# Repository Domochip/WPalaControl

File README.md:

# WPalaControl

**WPalaControl** is a Wi-Fi adapter (based on a D1 Mini) to control and monitor stoves using a **Fumis controller** (Palazzetti, Jotul, Godin, ...).

- 🔥 Power on/off, set point, power level, fans, silent mode, chrono programs, parameters
- 📊 Status, alarms, temperatures, counters, pellet consumption, delta pressure
- 🔌 Native HTTP API compatible with existing Palazzetti/Fumis apps and plugins
- 📡 MQTT with Home Assistant auto-discovery
- ⬆️ Online firmware update from GitHub (also as a Home Assistant Update entity)
- 🔒 Optional password protection of the web interface

## Contents

- [WPalaControl](#wpalacontrol)
  - [Contents](#contents)
  - [Quick start](#quick-start)
  - [Stove compatibility](#stove-compatibility)
  - [Home Automation compatibility](#home-automation-compatibility)
  - [Get your adapter](#get-your-adapter)
  - [Connect it to the stove](#connect-it-to-the-stove)
  - [First boot](#first-boot)
  - [Web interface](#web-interface)
    - [Status](#status)
    - [Config](#config)
      - [System](#system)
      - [WiFi](#wifi)
      - [PalaControl](#palacontrol)
      - [PalaControl - Home Automation](#palacontrol---home-automation)
    - [Firmware](#firmware)
  - [Use it](#use-it)
    - [HTTP](#http)
    - [MQTT](#mqtt)
  - [Command list](#command-list)
  - [Published MQTT values](#published-mqtt-values)
  - [Troubleshooting](#troubleshooting)
  - [Recovery Mode](#recovery-mode)

## Quick start

1. Check that your stove has a [Fumis controller](#stove-compatibility)
2. Plug the module into the stove with the provided cable (or the [right one](#connect-it-to-the-stove) if you built it yourself)
3. Connect to the `WPalaControl` Wi-Fi network (password: `password`)
4. In **Config**, enter your Wi-Fi credentials and save
5. Open <http://wpalacontrol.local>, then configure MQTT / Home Assistant if needed

## Stove compatibility

WPalaControl works with stoves using the **Fumis controller**, used by many manufacturers:

Palazzetti / Jotul / TurboFonte / Godin / Fonte Flamme / Invicta / Casatelli / Alpis / Faizen / HETA / ...

To check if your stove is compatible, look for one of these control panels or motherboards:

## Home Automation compatibility

| | Integration | Preview |
| --- | --- | --- |
|  | [MQTT Integration](https://www.home-assistant.io/integrations/mqtt/) (auto-discovery)<br>Most options and fan controls |  |
|  | [Palazzetti Integration](https://www.home-assistant.io/integrations/palazzetti)<br>(Home Assistant 2024.11 minimum)<br>Basic implementation for now |  |
|  | [Palazzetti plugin](https://www.jeedom.com/market/index.php?v=d&p=market_display&id=3104) |  |

## Get your adapter

- 🛍️ **Ready to use**: I produce small batches, available here:
  
- 🔧 **Build it yourself**: schematic, PCB, box and firmware are described in [BUILD](BUILD.md)

## Connect it to the stove

- ✅ If your stove has an accessible RJ12 connector, simply plug the cable in.
- 🔍 If not, you need an additional cable and a splitter: see [Splitter Cabling](SPLITTERCABLING.md).

If you bought your WPalaControl ready to use, the right cable is provided: simply use it.

> [!WARNING]
> If you built it yourself (or use another cable), use the correct cable for your hardware version (written on the PCB):
>
> - Hardware **V1.x**: **crossed** cable
> - Hardware **V2.x**: **straight** cable

## First boot

On first boot, the module creates its own Wi-Fi network (AP mode):

| Firmware | SSID | Password |
| --- | --- | --- |
| 3.2.0 and higher | `WPalaControl` | `password` |
| 3.1.x and lower | `WirelessPalaControlXXXX` | `PasswordPalaControl` |

You should be redirected to the module page automatically. If not, go to <http://192.168.4.1>.

Once the module is connected to your Wi-Fi network, it is reachable at 👉 <http://wpalacontrol.local> 👈

> [!NOTE]
> The access point is only started when the module is not connected to your Wi-Fi network (first boot, wrong settings, network down).

## Web interface

### Status

- **System**: module serial number, firmware version, uptime, local time (NTP) and free memory. Logged crashes are listed if any
- **WiFi**: MAC address, Access Point status (and IP), Station status with connection state, IP, IP source (DHCP or Static IP), BSSID and signal strength (RSSI)
- **WPalaControl**:
  - **Hardware Version**: detected (or forced) hardware version of the module
  - **Stove infos**: the stove SN appears first, then all stove values are refreshed live every "Upload Period" (values that changed are shown in bold)
  - **Home Automation Status**: protocol, MQTT connection state and result of the last publish

### Config

#### System

- **NTP Timezone**: your timezone, used for the module local time (default: Europe/Paris)
- **Web Password**: protects the web interface with a password (user: `admin`). Leave empty to disable authentication (default). The password is never requested from devices connected to the module's own Wi-Fi network (AP mode). The HTTP API used by home automation systems stays reachable without password for compatibility reasons (see [HTTP](#http))
- **Reboot**: restart the module
- **Reset Configuration**: erase all settings (System, WiFi, PalaControl) and restart the module with its default configuration (after a confirmation). The module then starts its own Wi-Fi network (AP mode, see [First boot](#first-boot)) and is reachable at <http://192.168.4.1>

#### WiFi

- **SSID & Password**: credentials of your Wi-Fi network. Nearby networks are listed in the dropdown next to the SSID field (strongest signal first)
- **Hostname**: name of the module on the network
- **Static IP**: check to use a fixed IP configuration instead of DHCP
  - **IP, NetMask, Gateway, DNS 1 & 2**: fixed IP configuration (IP is required)

Leave the SSID empty to keep the module in AP mode (reachable at <http://192.168.4.1>).

#### PalaControl

- **Hardware detection**: hardware version of the module
  - **Auto** (default): version is detected automatically at boot
  - **V1.X** / **V2.X**: force the hardware version if auto-detection fails

#### PalaControl - Home Automation

- **Type**: enable/disable MQTT communication
- **Upload Period**: refresh interval of stove information (15 to 300 seconds)
- **Hostname, Port, Username, Password**: MQTT broker details (username and password are optional)
- **Base Topic**: prefix of all WPalaControl topics
- **MQTT Type**: defines MQTT topics and data structure:
  - **Generic**: raw values under the base topic (e.g. `{baseTopic}/T1` = `20.00`)
  - **Generic JSON**: a JSON per category (e.g. `{baseTopic}/TMPS` = `{"INFO":{"CMD":"GET TMPS","RSP":"OK"},...}`)
  - **Generic Categorized**: raw values under a category topic (e.g. `{baseTopic}/TMPS/T1` = `20.00`)
- **Home Assistant Discovery**: enable/disable Home Assistant auto-discovery
  - **0.2° SetPoint step**: Set Point is adjusted in Home Assistant by 0.2°C steps (using `SET+STPF`) instead of 1°C steps (using `SET+SETP`). Only shown if Home Assistant Discovery is enabled and the stove supports it (air stoves)

### Firmware

- **Current Firmware**: version installed on the module
- **Online Update**: latest release published on [GitHub](https://github.com/Domochip/WPalaControl/releases) (version, title, date, summary and link)
  - **Refresh**: check GitHub again for the latest release
  - **Update**: download and install the latest release (enabled only if a newer version is available)
- **Manual Update**: upload a firmware file downloaded from the [releases page](https://github.com/Domochip/WPalaControl/releases)
  - Expected file name: `WPalaControl.x.y.z.bin`
  - Older `WirelessPalaControl.*.bin` files are also accepted

> [!CAUTION]
> Do not power off the module during the update. It reboots automatically when the update is done.

- ℹ️ Online Update requires Internet access from the module (not available in AP mode). If you configured a static IP, make sure Gateway and DNS are set (not needed with DHCP).
- 🏠 With MQTT and Home Assistant Discovery enabled, a firmware **Update** entity is also available in Home Assistant (checked once a day).

## Use it

Commands are the same for HTTP and MQTT: see the [Command list](#command-list).

### HTTP

Send an HTTP GET request to the module:

```text
http://wpalacontrol.local/cgi-bin/sendmsg.lua?cmd={command}
```

This API never requires the **Web Password**, so existing apps and plugins keep working when it is set.

Example: `http://wpalacontrol.local/cgi-bin/sendmsg.lua?cmd=GET+TMPS` returns:

```json
{"INFO":{"CMD":"GET TMPS","RSP":"OK"},"DATA":{"T1":20.6,"T2":21,"T3":18,"T4":0,"T5":0},"SUCCESS":true}
```

### MQTT

Once MQTT is configured, send commands to the `{baseTopic}/cmd` topic:

```bash
mosquitto_pub -h <broker> -t "WPalaControl/cmd" -m "SET+SETP+21"
```

The result is:

- published following the configured MQTT Type
- published on `{baseTopic}/result` in JSON format

Other topics published by the module:

| Topic | Content |
| --- | --- |
| `{baseTopic}/connected` | `0`: not connected / `1`: connected but no communication with the stove / `2`: module and stove connected |
| `{baseTopic}/Core` | Module status in JSON (manufacturer, model, sn, version, uptime, localtime, freeheap), refreshed every "Upload Period" |
| `{baseTopic}/WiFi` | Wi-Fi status in JSON (apmode, stationmode, stationip, bssid, rssi, ...), refreshed every "Upload Period" |
| `{baseTopic}/App` | WPalaControl status in JSON (hwversion, hwdetection, MQTT status, last publish result, ...), refreshed every "Upload Period" |
| `{baseTopic}/update` | Latest available firmware update information |
| `{baseTopic}/update/install` | Command topic to trigger a firmware update (used by Home Assistant) |

## Command list

⏲️: Published automatically every "Upload Period" (MQTT)  
✨: WPalaControl specific command

| Command | Description | Values | Notes |
| ------- | ----------- | ------ | :---: |
| `GET+STDT` | Get static data | | |
| `GET+ALLS` | Get all status data | | |
| `GET+STAT` | Get stove status | | ⏲️ |
| `GET+TMPS` | Get stove temperatures | | ⏲️ |
| `GET+FAND` | Get fan values | | ⏲️ |
| `GET+SETP` | Get current Set Point (desired temperature) | | ⏲️ |
| `GET+POWR` | Get current power | 1-5 | ⏲️ |
| `GET+CUNT` | Get counters | | |
| `GET+CNTR` | Get counters (same as `GET+CUNT`) | | ⏲️ |
| `GET+DPRS` | Get delta pressure data | | ⏲️ |
| `GET+TIME` | Get stove clock data | | ⏲️ |
| `GET+IOPT` | Get IO ports status | | |
| `GET+SERN` | Get stove Serial Number | | |
| `GET+MDVE` | Get stove model and firmware version | | |
| `GET+CHRD` | Get chrono data | | |
| `GET+PARM+92` | Get parameter (e.g. 92 = pellet type) | parameter number | |
| `GET+HPAR+57` | Get hidden parameter (e.g. 57 = % of pellet to feed for pellet type 3) | parameter number | |
| `BKP+PARM+CSV` | Get all parameters in a CSV file (HTTP only) | | ✨ |
| `BKP+PARM+JSON` | Get all parameters in a JSON file (HTTP only) | | ✨ |
| `BKP+HPAR+CSV` | Get all hidden parameters in a CSV file (HTTP only) | | ✨ |
| `BKP+HPAR+JSON` | Get all hidden parameters in a JSON file (HTTP only) | | ✨ |
| `CMD+ON` | Turn stove ON | | |
| `CMD+OFF` | Turn stove OFF | | |
| `SET+POWR+3` | Set power | 1-5 | |
| `SET+PWRU` | Increase power by 1 unit | | |
| `SET+PWRD` | Decrease power by 1 unit | | |
| `SET+SETP+20` | Set Set Point (desired temperature) | temperature | |
| `SET+STPF+19.8` | Set Set Point with 0.2°C precision (depends on your stove model) | temperature | ✨ |
| `SET+STPU` | Increase Set Point by 1 unit | | |
| `SET+STPD` | Decrease Set Point by 1 unit | | |
| `SET+RFAN+7` | Set Room Fan value | 0-5; 6=Max; 7=Auto | |
| `SET+FN2U` | Increase Room Fan by 1 unit | | |
| `SET+FN2D` | Decrease Room Fan by 1 unit | | |
| `SET+FN3L+0` | Set Room Fan 3 value | 0-5 | |
| `SET+FN4L+0` | Set Room Fan 4 value | 0-5 | |
| `SET+SLNT+0` | Set Silent mode | 0-1 | |
| `SET+TIME+2023-12-28+19:42:00` | Set stove date and time | year 2000-2099, month 1-12, day 1-31, hour 0-23, min 0-59, sec 0-59 | |
| `SET+CSST+0` | Set Chrono status | 0-1 | |
| `SET+CSTH+2+18` | Set Chrono Program start hour | prog 1-6, hour 0-23 | |
| `SET+CSTM+2+30` | Set Chrono Program start minute | prog 1-6, min 0-59 | |
| `SET+CSPH+2+22` | Set Chrono Program stop hour | prog 1-6, hour 0-23 | |
| `SET+CSPM+2+45` | Set Chrono Program stop minute | prog 1-6, min 0-59 | |
| `SET+CSET+2+19` | Set Chrono Program Set Point | prog 1-6, temperature | |
| `SET+CDAY+7+3+6` | Set Chrono Program for a week day (Day-Mem-Prog) | day 1-7, mem 1-3, prog 1-6 | |
| `SET+CPRD+1+19+18+30+22+45` | Set Chrono Program data (Prog-Temp-StartH-StartM-StopH-StopM) | prog 1-6, temperature, 0-23, 0-59, 0-23, 0-59 | |
| `SET+PARM+92+2` | Set parameter 92 to value 2 (pellet type) | parameter number, value (e.g. 1-3 for 92) | |
| `SET+HPAR+57+95` | Set hidden parameter 57 to value 95 (% of pellet to feed for pellet type 3) | parameter number, value | |

## Published MQTT values

Values published automatically every "Upload Period":

| Key | Meaning | Unit |
| --- | ------- | ---- |
| `STATUS`, `LSTATUS`, `FSTATUS` | Stove status | |
| `T1`, `T2`, `T3`, `T4`, `T5` | Stove temperatures | °C |
| `F1V`, `F2V`, `F2L`, `F2LF` | Fan values (meaning depends on your stove model) | |
| `F1RPM` | Fan 1 speed | rpm |
| `F3L`, `F4L` | Fan 3 / Fan 4 levels (if supported by the stove) | 0-5 |
| `F3S`, `F4S` | Fan 3 / Fan 4 values (if supported by the stove) | |
| `IGN` | Ignition counter | |
| `IGNERRORS` | Ignition error counter | |
| `POWERTIME` | Total heating time | hour:minute |
| `HEATTIME` | Unknown meaning | hour:minute |
| `SERVICETIME` | Heating time since last maintenance | hour:minute |
| `ONTIME` | Time since last power ON | hour:minute |
| `OVERTMPERRORS` | Overtemperature error counter | |
| `PQT` | Wood pellet consumption | kg |
| `STOVE_DATETIME` | Stove date and time | |
| `STOVE_WDAY` | Stove week day | |
| `SETP` | Current Set Point (desired temperature) | °C |
| `SECO` | ECO Mode restart temperature threshold (PAR50: 6 -> 0.6°C) | °C |
| `BECO` | ECO Mode active | |
| `PWR` | Current power | 1-5 |
| `FDR` | Feeder | |
| `DP_TARGET` | Delta pressure target | mPa |
| `DP_PRESS` | Actual delta pressure | mPa |

## Troubleshooting

| Problem | What to check |
| --- | --- |
| Stove SN never appears on the Status page | Use the provided cable. If you built it yourself, check the cable type: **crossed** for hardware V1.x, **straight** for V2.x. Check also the **Hardware detection** setting |
| `wpalacontrol.local` does not open | Some devices (e.g. Android, some Windows setups) don't support mDNS: use the module IP address (shown in your router) |
| Wrong Wi-Fi settings, module unreachable | If it can't connect, the module starts its own access point: connect to it and go to <http://192.168.4.1>. You can also press the RST button 3 times to start in [Recovery Mode](#recovery-mode) |
| Web Password forgotten | Press the RST button 3 times to start in [Recovery Mode](#recovery-mode): the password is not requested, so you can change it in **Config** → **System** |
| Online Update fails | The module needs Internet access. If you configured a static IP, make sure Gateway and DNS are set (not needed with DHCP) |
| Nothing published on MQTT | **Status** page → **Home Automation Status** shows the connection state and the last publish result |

## Recovery Mode

Recovery Mode gives you access to the module when you can't reach it normally, without losing its configuration. Use it when:

- the module can't be reached after a Wi-Fi settings change (wrong SSID, password or static IP)
- you forgot the **Web Password**

**Enter Recovery Mode**:

- press the **RST** button (accessible on the side of the box) **3 times in a row**, each press within 5 seconds of the previous one
- only presses of the RST button are counted: unplugging/replugging the module does not trigger Recovery Mode

**In Recovery Mode**:

- the module does not connect to your Wi-Fi network: it only starts its own (SSID and password in [First boot](#first-boot)). Connect to it and go to <http://192.168.4.1>
- the **Web Password** is not requested
- the stored configuration is loaded but not modified: nothing is erased

**Leave Recovery Mode**:

- save any configuration section (e.g. **Config** → **WiFi** or **Config** → **System**), after a confirmation: the module goes back to normal operation immediately (connection to your Wi-Fi network, **Web Password** if set). Reconnect your device to your Wi-Fi network and open the module address
- or reboot the module: it starts normally with its stored configuration

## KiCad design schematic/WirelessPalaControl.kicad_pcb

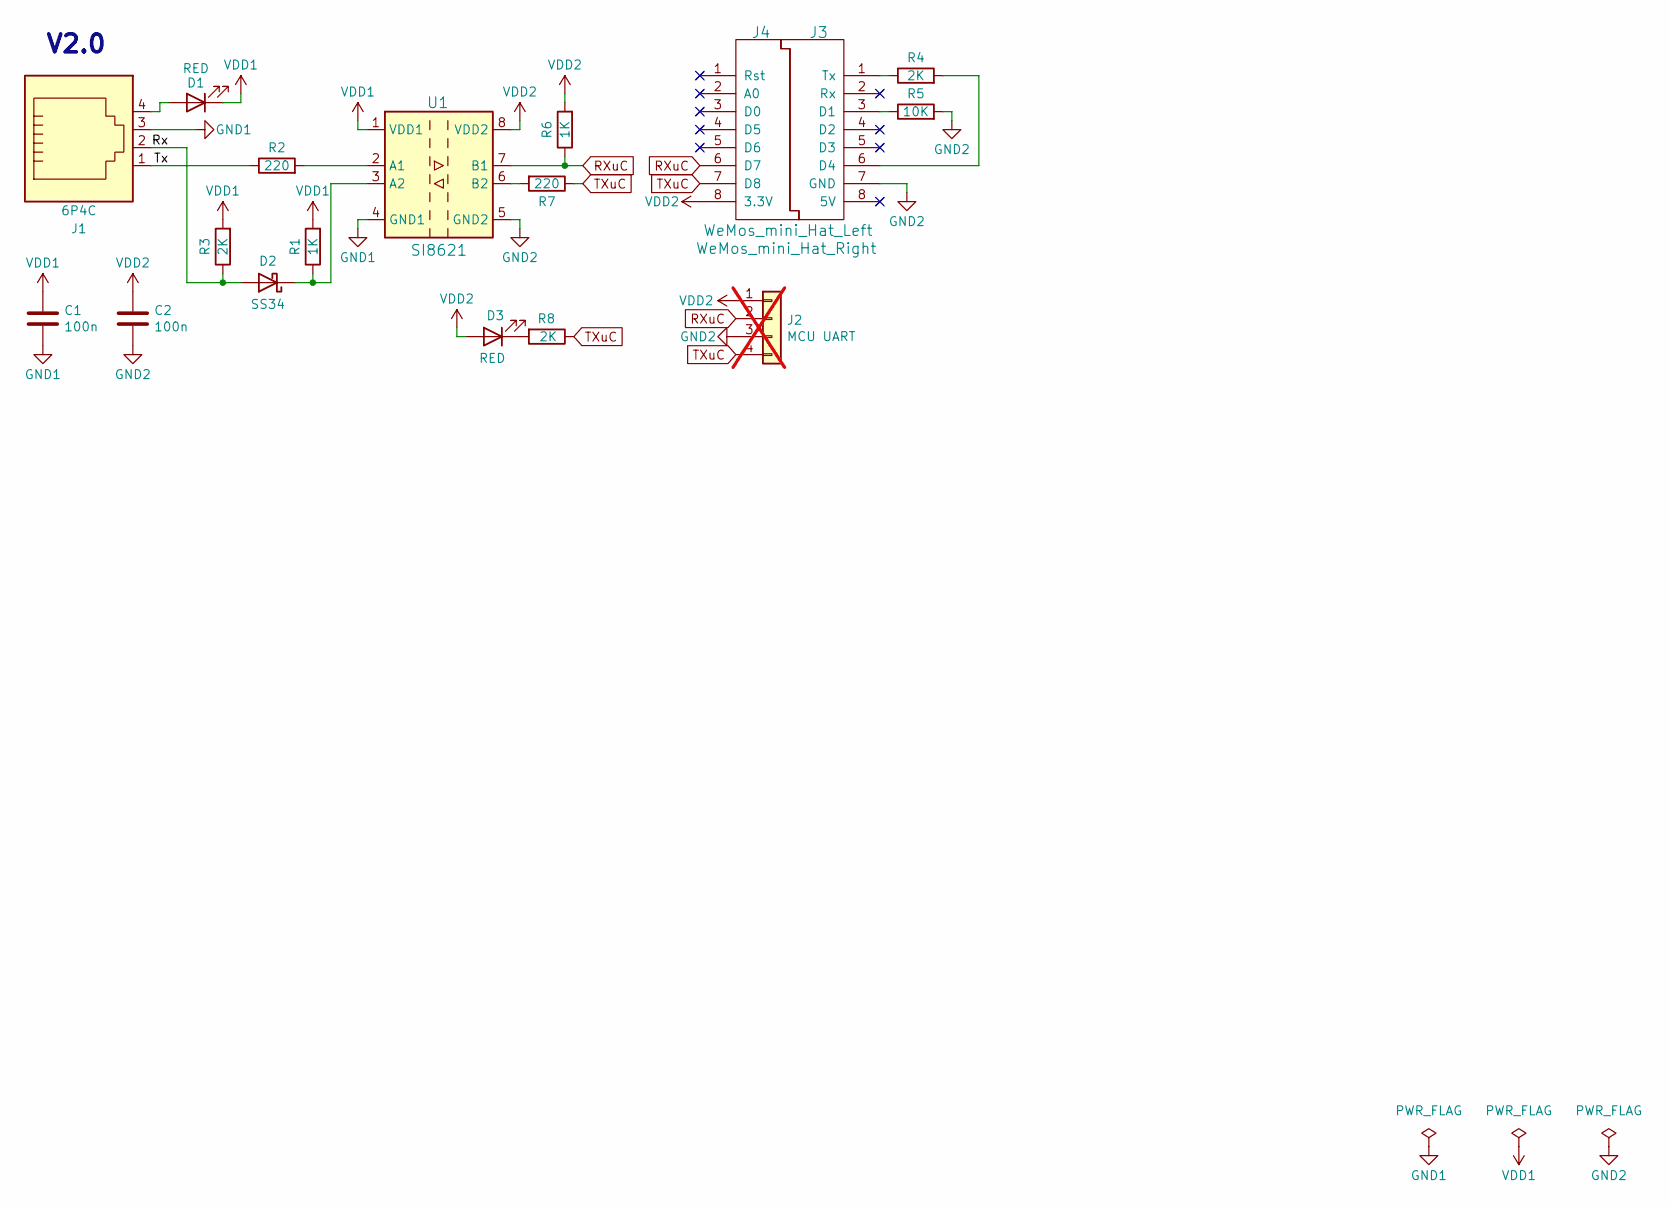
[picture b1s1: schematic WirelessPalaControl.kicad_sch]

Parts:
C1, C2: 100n; C_0805_2012Metric_Pad1.18x1.45mm_HandSolder; LCSC C49678
D1, D3: RED; LED_0805_2012Metric_Pad1.15x1.40mm_HandSolder; LCSC C84256
D2: SS34; D_SMA; LCSC C8678
J1: 6P4C; Ali_RJ11; LCSC C189749
J2: MCU UART; PinHeader_1x04_P2.54mm_Vertical; not fitted
J3: WeMos_mini_Hat_Left; WeMos_D1_mini_Hat_Left; LCSC C7509515
J4: WeMos_mini_Hat_Right; WeMos_D1_mini_Hat_Right; LCSC C7509515
R1, R6: 1K; R_0805_2012Metric_Pad1.20x1.40mm_HandSolder; LCSC C17513
R2, R7: 220; R_0805_2012Metric_Pad1.20x1.40mm_HandSolder; LCSC C17557
R3, R4, R8: 2K; R_0805_2012Metric_Pad1.20x1.40mm_HandSolder; LCSC C17604
R5: 10K; R_0805_2012Metric_Pad1.20x1.40mm_HandSolder; LCSC C17414
U1: SI8621; SOIC-8_3.9x4.9mm_P1.27mm; LCSC C461877

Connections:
/Rx: D2.2 (A), J1.2, R3.1
/Tx: J1.1, R2.1
GND1: C1.2, J1.3, U1.4 (GND1)
GND2: C2.2, J2.3, J3.7 (GND), R5.2, U1.5 (GND2)
unnamed: D1.2 (A), J1.4
unnamed: D2.1 (K), R1.1, U1.3 (A2)
unnamed: D3.1 (K), R8.2
unnamed: J3.3 (D1), R5.1
unnamed: J3.6 (D4), R4.2
unnamed: J3.1 (Tx), R4.1
unnamed: R2.2, U1.2 (A1)
unnamed: R7.2, U1.6 (B2)
RXuC: J2.2, J4.6 (D7), R6.1, U1.7 (B1)
TXuC: J2.4, J4.7 (D8), R7.1, R8.1
VDD1: C1.1, D1.1 (K), R1.2, R3.2, U1.1 (VDD1)
VDD2: C2.1, D3.2 (A), J2.1, J4.8 (3.3V), R6.2, U1.8 (VDD2)

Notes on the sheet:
V2.0

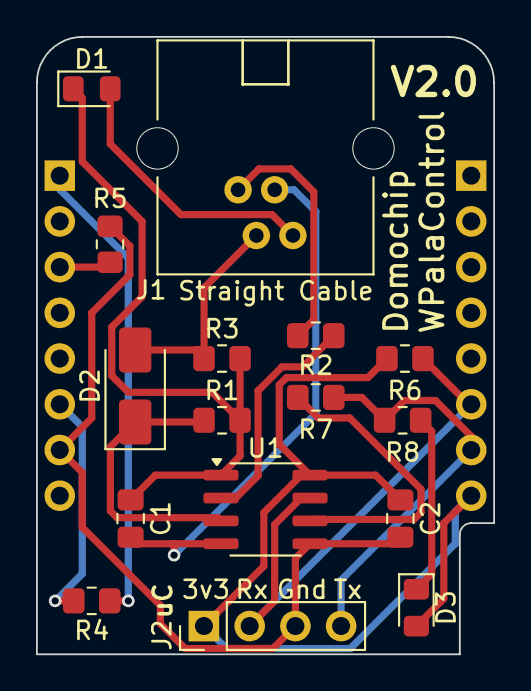
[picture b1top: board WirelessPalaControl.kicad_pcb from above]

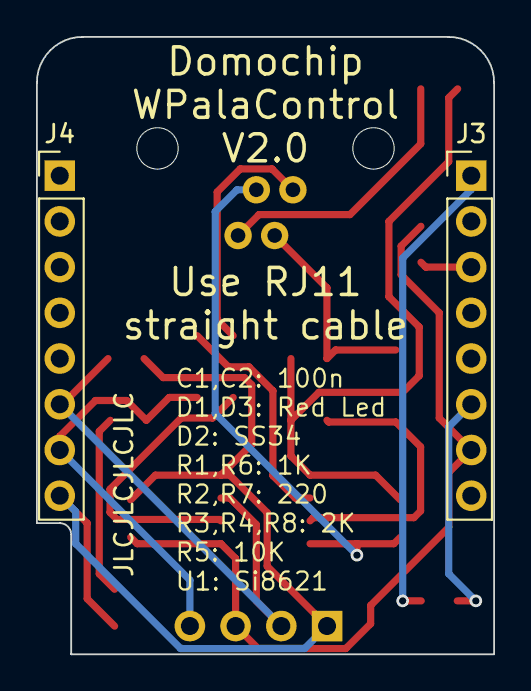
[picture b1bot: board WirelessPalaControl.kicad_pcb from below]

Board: 2 copper layers, 25.4 x 34.3 mm, 18 parts (2 on the bottom side), 16 nets.

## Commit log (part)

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2024-11-12 Rollback duplication of code
2024-11-12 Determine the Main temperature sensor
2024-11-12 Use name for the Main temperature sensor
2024-11-12 Add additionnal sensors for Hydro
2024-11-12 Revert to Room instead of Ambient
2024-11-12 Use Storage Tank wording like docs
2024-11-13 Comment 2nd and 3rd sensor until clarification
2024-11-13 Approach based on Android App
2024-11-13 Better limit condition
2024-11-15 Group FlashString lists
2024-11-15 More usefull variables grouped
2024-11-15 Use new tempProbeTopicListArray variable
2024-11-15 Add Thermostat (climate) entity
2024-11-15 Add Power command to Thermostat
2024-11-15 Add temperature command topic
2024-11-15 Simplify jinja template
2024-11-15 Add Fan management
2024-11-15 Improve jinja templates
2024-11-16 One more usefull flashString
2024-11-23 Change R4 to 2K
2024-11-23 Update schematic and botoom pcb
2024-11-24 Slightly adjust box
2025-09-24 Update schematic and pcb to KiCAD 9
2025-09-25 Adapt WPalaControl for 256dpi/MQTT lib
2025-09-26 Switch to PubSubClient3 lib which is maintained
2025-09-26 Increase MQTT buffer size
2025-09-27 Add coming "default_entity_id" for Home Assistant 2025.10
2025-10-24 Fixed an issue where the WiFi reconnection routine (`_refreshTicker.once()`) never triggered when the initial connection failed. The delay value was incorrectly multiplied by 1000, causing the timer 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
2025-12-22 Fix FAN3 & FAN4 not showing up in Home Assistant
2025-12-23 Fix FAN3 & FAN4 not showing up in Home Assistant (#79)
2025-12-23 Bump version to 3.5.1
2025-12-30 Fix incorrect default_entity_id values
2025-12-30 Bump version to 3.5.2
2026-04-07 Add variables for detection
2026-04-07 Add config field to choose detection mode
2026-04-07 Implement logic for autodetection/forced mode
2026-04-07 Add detection infos on status page
2026-04-07 Force Hardware version instead of autodetection (#87)
    * Add variables for detection
    * Add config field to choose detection mode
    * Implement logic for autodetection/forced mode
    * Add detection infos on status page
2026-04-07 Bump version to 3.5.3
2026-05-13 Update schematic to KiCAD 10
2026-05-13 Reduce String allocation/concatenation in GET CNTR
2026-05-13 Reduce usage of heap
2026-05-13 Factorize baseTopic substring call
2026-05-13 Avoid usage of String.replace to validate strtol conversion
2026-05-13 change type of palaCategory
2026-05-14 Adjust ConfigJSON and StatusJSON functions
2026-05-14 eventSourceBroadcast parameter type is now a char array
2026-05-14 Adapt mqttPublishUpdate according to new parameters an type of fillLatestUpdateInfoJson
2026-05-14 Refactor PalaCmd execution
2026-05-14 Building baseTopic only if required
2026-05-14 Avoid creating a String in heap to check the content
2026-05-15 Adjust for Base 2.7.0
2026-05-15 Revert "Avoid creating a String in heap to check the content"
    This reverts commit 248da516b3f21e527d812d21de225210121652b0.
2026-05-17 Adjust for Base 2.7.1
2026-05-17 Bump version to 3.6.0
2026-05-17 Bump version to 3.6.1
2026-05-18 Format
2026-05-18 Add _preparedMqttBaseTopic variable
2026-05-18 Adjust for Base 2.7.4
2026-05-18 Remove intermediate String to send result of pala command
2026-05-18 Use new eventSourceBroadcast signature
2026-05-18 Use new MQTTMan::publish signature
2026-05-18 Improve mqttPublishData to avoid String and Heap fragmentation
2026-05-18 Avoid String usag to convert float in palaCmd execution
2026-05-18 Reserve memory space for CSV backup to avoid fragmentation
2026-05-18 Avoid intermediate String for JSON backup
2026-05-18 Reduce String reallocation in Backup endpoint result construction
2026-05-18 Rewrite of cmd parameters parsing without String and Fix STPF
2026-05-19 Bump version to 3.6.2
2026-05-19 Add d1_mini_debug platformio env
2026-05-19 Add new VERSION definition
2026-05-20 Remove tempPassword variable
2026-05-20 Use new WifiMan::ipToCString helper
2026-05-20 Remove publishJson helper
2026-05-20 availabilityJSON in mqttPublishHassDiscovery is predefined
2026-05-20 mqttPublishHassDiscovery uses deserialized JSON for fixed value in payloads
2026-05-20 Dispatch const which are used only once
2026-05-20 mqttPublishUpdate uses deserialized JSON for fixed value in payloads
2026-05-21 Adjust for Base 2.7.11
2026-05-21 Adapt for Base 2.7.12
2026-05-21 Improve pio ini file according to WBase
2026-05-21 Rename JsonDocument variables
2026-05-21 Reorganize appInitWebServer lambda code for readability
2026-05-22 Fix bug in SET TIME parameters validation
2026-05-22 Avoid overflow risk
2026-05-22 Replace widely used configuration macros by enums
2026-05-22 Fix lambda type specification in appInit for publish tickers
2026-05-22 Fix ESP32 serialization to http client
2026-05-22 Move default parameter value to header files instead of cpp
2026-05-22 Rename prepareEntityTopic to prepareHassDiscoveryTopic
2026-05-22 Reserve topic length to avoid heap fragmentation
2026-05-22 prefix is always _ha.mqtt.hassDiscoveryPrefix
2026-05-22 Move prepareHassDiscoveryTopic helper as a method
2026-05-22 Move this module Hass discovery to a dedicated function
2026-05-22 Move Stove Hass discovery to a dedicated function
2026-05-22 Reorder code
2026-05-22 Add buildStoveDeviceString function
2026-05-22 Create HassDiscoveryStoveContext
2026-05-22 Methods renaming and Add Stove Connectivity sub function
2026-05-22 Add mqttPublishHassStoveStatus
2026-05-22 Add all other entity methods
2026-05-22 Cleanup
2026-05-22 Remove intermediate variables
2026-05-22 Reorder merhods
2026-05-23 Split executeGetPalaCmd into small methods
2026-05-23 Move executeCmdPalaCmd
2026-05-23 Split executeCmdPalaCmd into small methods
2026-05-23 Split executeSetPalaCmd into small methods
2026-05-23 Move executePalaCmdSet* functions
2026-05-23 Split executeExtPalaCmd into small methods
2026-05-23 Move executePalaCmdExt* functions
2026-05-23 Switch selling to Lectronz
2026-05-24 Revert changes on WPalaControl.h/.cpp back to commit "prefix is always _ha.mqtt.hassDiscoveryPrefix" e1e83e4ed1ef5584f8e8446502f4a0b80288fe3b
2026-05-24 Rename executePalaCmd subfunctions
2026-05-24 Bump version to 3.6.3
2026-05-24 Adjust for Palazzetti lib 2.7.10
2026-05-24 DP_TARGET will never go over 7FFF (->546Pa)
2026-05-25 Adapt Palazzetti lib initialization code
2026-05-25 Adapt mqttPublishHassDiscovery for the new Palazzetti lib structs
2026-05-25 Adapt palaCmd execution for the new Palazzetti lib structs
2026-05-25 Update plzbridge version
2026-05-26 Add FSTATUS to the GET ALLS returned values
2026-05-26 Add SEC/BECO to the GET SETP returned values
2026-05-26 Rename Return variables to Result variables
2026-05-26 Use new variable type for POWERTIME, HEATTIME, SERVICETIME, ONTIME
2026-05-26 Add EFLGAS to the GET ALLS returned values
2026-05-26 Add PLEVEL,PSENSCSTA,PSENSLEMP to the GET ALLS returned values
2026-05-26 Add SET FN3S/FN4S commands
2026-05-26 Update sendmsg & SYSTEM values for GET STDT
2026-05-27 shrinkToFit reorganizes memory used but then data and info are pointer to freed memory
2026-05-27 Clean up getHTMLContent and getHTMLContentSize switch cases
2026-05-28 Bump version to 3.7.0
2026-05-28 Adapt for Base 2.8.0
2026-05-28 Webpage includes moved from h file to cpp
2026-05-28 Adapt for Base 2.8.2
2026-05-28 Adapt for Base 2.9.0
2026-05-28 Remove index.html
2026-05-28 Add index.html to .gitignore
2026-05-29 Comments
2026-05-29 Adapt for Base 2.9.4
2026-05-29 Move config validation code into validateConfig()
2026-05-29 Adapt for Base 2.9.6
2026-06-01 Bump version to 3.7.1
2026-06-03 Use lambas instead of std::bind for _mqttMan callbacks
2026-06-03 Use lambas instead of std::bind for _Pala callbacks
2026-06-03 Use WifiMan::getMacAddress()
2026-06-03 Move Update HomeAssistant entity to mqttPublishHassDiscovery
2026-06-03 HomeAssistant in_progress flag move to Base
2026-06-03 Minor improvements
2026-06-06 Replace byte by uint8_t
2026-06-07 Adapt for Base 2.9.10
2026-06-07 Rename prepareHassDiscoveryTopic helper to prepareTopic
2026-06-07 Move prepareTopic helper
2026-06-07 use a publishEntity helper in mqttPublishHassDiscovery
2026-06-07 Refactor mqttPublishHassDiscovery to use setValueTemplate helper for value_template assignment
2026-06-07 Add getStateTopic helper for state topic assignments in mqttPublishHassDiscovery
2026-06-07 Replace last flash array usage by getStateTopic
2026-06-07 Fix typo
2026-06-07 Add requireParams helper in executePalaCmdSet to verify parameter number
2026-06-11 Change how module status is published on MQTT
2026-06-11 Add WiFi connection counter entity to MQTT discovery
2026-06-11 Add MQTT connection count to status JSON
2026-06-11 Add MQTT connection counter entity to Hass discovery
2026-06-11 Comment
2026-06-12 Adapt for Base 2.9.13
2026-06-12 Use new mqttPublishHassDiscovery simpler and more organized part 1
2026-06-12 Refactor mqttPublishHassDiscovery to improve structure and readability; add mqttPublishStoveHassDiscovery method
2026-06-12 Clean retained message on base topic in mqttConnectedCallback
2026-06-13 Adapt for Base 2.10.1
2026-06-13 Remove dead code
2026-06-13 Adjust availability of Stove Device in Hass
2026-06-13 Adapt for Base 2.10.2
2026-06-15 Adapt for Base 2.10.3
2026-06-15 Bump version to 3.7.2
2026-06-15 Adapt for Base 2.10.5
2026-06-15 Add MQTT last disconnect reason to status JSON
2026-06-15 Add MQTT last disconnection reason to Home Assistant Discovery
2026-06-16 Update MQTT disconnection icon in Hass discovery JSON
2026-06-16 redirectWhenReachable can be called directly instead of using loadScript
2026-06-16 Add two addFloat helpers in executePalaCmdGet and executePalaCmdSet functions
2026-06-17 Add setTemplateField helper to simplify Home Assistant autodiscover
2026-06-17 Fix ESP32 compilation problem
2026-06-17 Bump version to 3.7.3
2026-06-17 Reduce MQTT buffer size to 512 bytes
2026-06-18 Simplify parseConfigJSON and fillConfigJSON
2026-06-18 C++ style struct
2026-06-18 Remove default values from header
2026-06-18 Adapt for Base 2.10.9
2026-06-18 Adapt for Base 2.10.10
2026-06-19 Adapt for Base 2.10.11
